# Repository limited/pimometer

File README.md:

pimometer
=========
=======
## Remote Thermocouple Monitor

### Goal 
PCB to report temperature from 4 k-type thermocouples over wireless, for viewing on a smartphone. 
* _Form Factor_: Raspberry Pi Shield
* _Power Source_: Initially battery powered with on/off switch. 
** Future: solar or thermoelectric generator(TEG) using heat from oven.
* _Thermocouple Measurement_: MAX31855 [Datasheet](http://datasheets.maximintegrated.com/en/ds/MAX31855.pdf) via SPI in an SO-8 package
* _Wireless Connection_: WiFi Dongle
* _Configuration/Display_: via SD Card 
** LEDs for display- 1 LED for wireless connection
* Smartphone Display: Ideally would be accessible across multiple smartphone platforms, so no native app. 
** Better to have a webserver run on the device itself, i.e. Flask

### Design
#### Raspberry Pi pinout
* Clock: 11 
* MISO: 9
* CS1: 18 
* CS2: 23
* CS3: 24
* CS4: 25
* Also need +3.3V and ground available to shield
 
#### Software Design
* When Flask receives request for current temperatures, 
o

#### Service installation
chmod 755 nodejs
sudo cp nodejs /etc/init.d
sudo update-rc.d nodejs defaults

### Avahi Installation
sudo apt-get install avahi-daemon
sudo insserv avahi-daemon

#### Cost Comparison
Component  |  Raspberry Pi  | Arduino (TC shield + wifi breakout)
-----------+----------------+-------------------------------------
Controller |   $35          |    $7
Crystal    |                |    $1
Regulator  |                |    $2
Wifi       |   $15          |    $35
SD card    |   $8           |    
------------------------------------------------------------------
Subtotal   |   $58          |    $45

TC shield
------------
4xTC       |              $32
Custom PCB |              $15?

Enclosure    |
LiPo Battery | 
LiPo Charger |

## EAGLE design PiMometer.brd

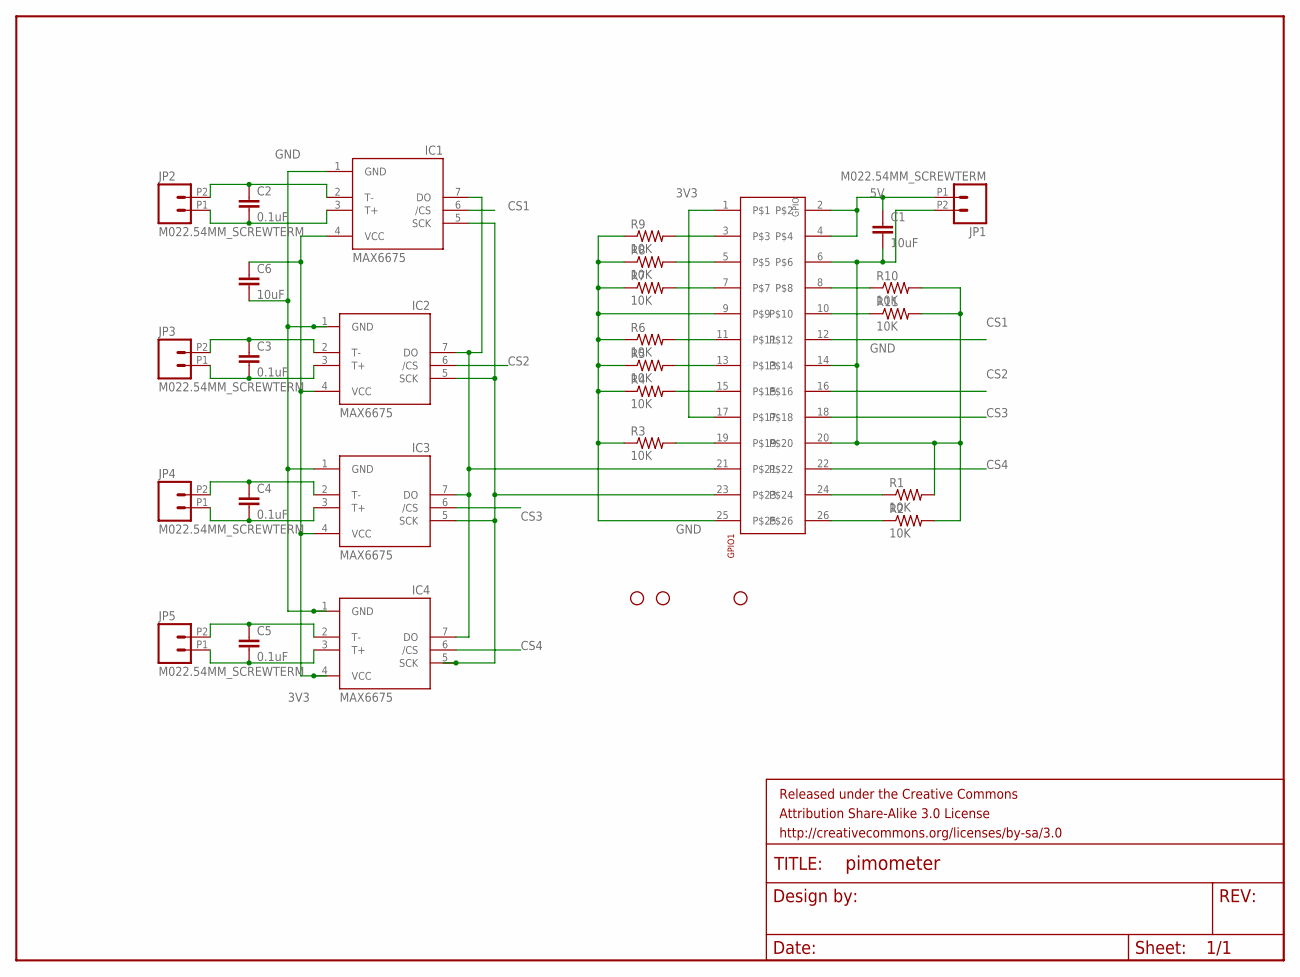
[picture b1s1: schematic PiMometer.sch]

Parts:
C1, C6: 10uF; 1210
C2, C3, C4, C5: 0.1uF; 0603-CAP
FRAME1: FRAME-LETTER; CREATIVE_COMMONS
GPIO1: 2X132X13; 2X13
IC1, IC2, IC3, IC4: MAX6675; SO08
JP1, JP2, JP3, JP4, JP5: M022.54MM_SCREWTERM; 1X02_2.54_SCREWTERM
R1, R2, R3, R4, R5, R6, R7, R8, R9, R10, R11: 10K; 0603-RES
STANDOFF1, STANDOFF2, STANDOFF4: STAND-OFF

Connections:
3V3: C6.1, GPIO1.1, GPIO1.17, IC1.4 (VCC), IC2.4 (VCC), IC3.4 (VCC), IC4.4 (VCC)
5V: C1.1, GPIO1.2, GPIO1.4, JP1.P1 (1)
CS1: GPIO1.12, IC1.6 (/CS)
CS2: GPIO1.16, IC2.6 (/CS)
CS3: GPIO1.18, IC3.6 (/CS)
CS4: GPIO1.22, IC4.6 (/CS)
GND: C1.2, C6.2, GPIO1.6, GPIO1.9, GPIO1.14, GPIO1.20, GPIO1.25, IC1.1 (GND), IC2.1 (GND), IC3.1 (GND), IC4.1 (GND), JP1.P2 (2), R1.2, R2.2, R3.1, R4.1, R5.1, R6.1, R7.1, R8.1, R9.1, R10.2, R11.2
unnamed: GPIO1.21, IC1.7 (DO), IC2.7 (DO), IC3.7 (DO), IC4.7 (DO)
unnamed: GPIO1.23, IC1.5 (SCK), IC2.5 (SCK), IC3.5 (SCK), IC4.5 (SCK)
unnamed: GPIO1.24, R1.1
unnamed: GPIO1.26, R2.1
unnamed: C2.1, IC1.2 (T-), JP2.P2 (2)
unnamed: C2.2, IC1.3 (T+), JP2.P1 (1)
unnamed: GPIO1.3, R9.2
unnamed: GPIO1.5, R8.2
unnamed: GPIO1.7, R7.2
unnamed: GPIO1.11, R6.2
unnamed: GPIO1.13, R5.2
unnamed: GPIO1.15, R4.2
unnamed: GPIO1.19, R3.2
unnamed: GPIO1.8, R10.1
unnamed: GPIO1.10, R11.1
unnamed: C3.1, IC2.2 (T-), JP3.P2 (2)
unnamed: C3.2, IC2.3 (T+), JP3.P1 (1)
unnamed: C4.1, IC3.2 (T-), JP4.P2 (2)
unnamed: C4.2, IC3.3 (T+), JP4.P1 (1)
unnamed: C5.1, IC4.2 (T-), JP5.P2 (2)
unnamed: C5.2, IC4.3 (T+), JP5.P1 (1)

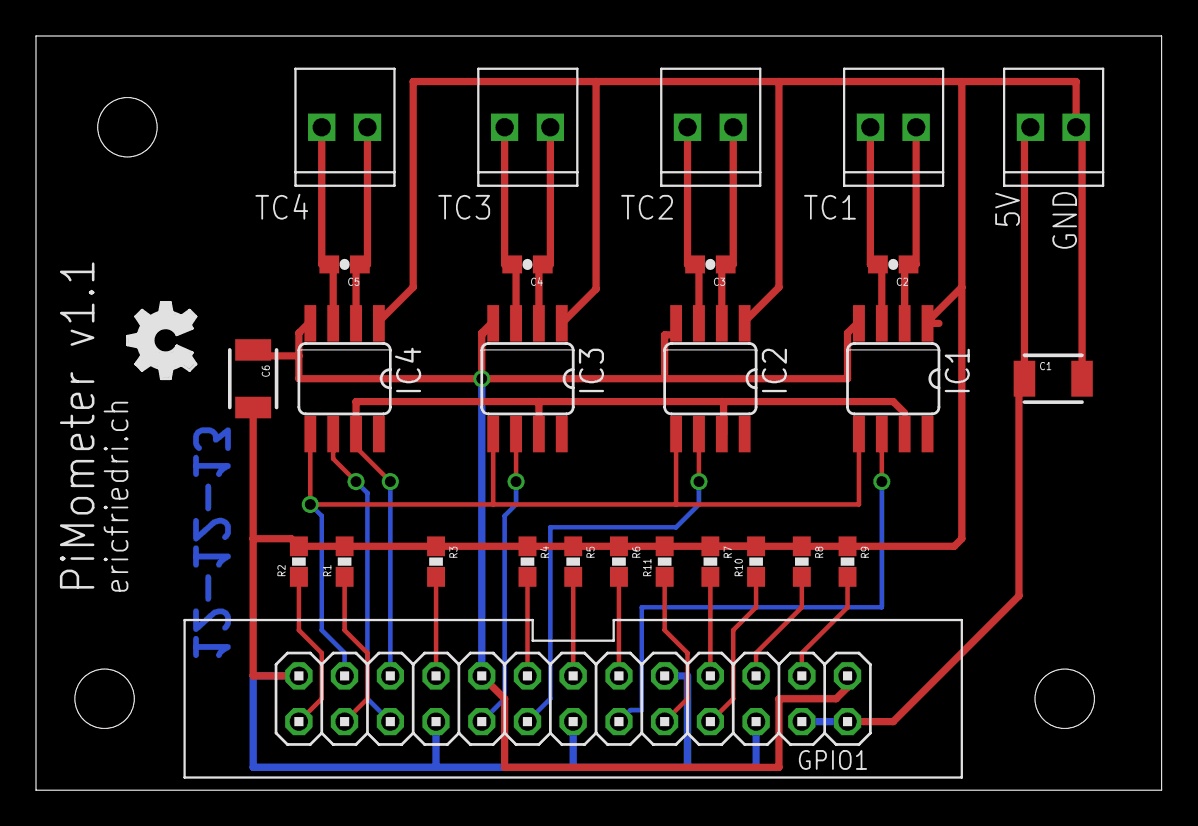
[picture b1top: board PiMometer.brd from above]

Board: 2 copper layers, 62.5 x 41.9 mm, 32 parts (0 on the bottom side), 28 nets.

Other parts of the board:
U$1: OSHW_FILLX150_NOTEXT

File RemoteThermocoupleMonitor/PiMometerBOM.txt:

Partlist exported from /Users/efriedri/Dropbox/eagle/PiMometer/PiMometer.sch at 11/29/13 10:36 PM

(M) Mouser
(SF) Sparkfun

Supplier	Part      Value               Device                  Package             Description                          PROD_ID   VALUE
M		C1        10uF                10UF50V20%(1210)        1210                16V 1210 10uF 10% MLCC	       810-C3225X7R1C106K 10uF 
M		C2        0.1uF               0.1UF-100V-10%(0603)    0603-CAP            16V 0603 .1uF 5% MLCC                77-VJ0603Y104JXJPBC 0.1uF
M		C3        0.1uF               0.1UF-100V-10%(0603)    0603-CAP            16V 0603 .1uF 5% MLCC                77-VJ0603Y104JXJPBC 0.1uFM
M		C4        0.1uF               0.1UF-100V-10%(0603)    0603-CAP            16V 0603 .1uF 5% MLCC                77-VJ0603Y104JXJPBC 0.1uF
M		C5        0.1uF               0.1UF-100V-10%(0603)    0603-CAP            16V 0603 .1uF 5% MLCC                77-VJ0603Y104JXJPBC 0.1uF
M		C6        10uF                10UF50V20%(1210)        1210                16V 1210 10uF 10% MLCC               810-C3225X7R1C106K 10uF                                    
SF		GPIO1     2X132X13            2X132X13                2X13                PRT-11490                            PRT-11490                                                      
M		IC1       MAX31855            MAX31855 		      SO08      	  MAX31855KASA+                                                              
M		IC2       MAX31855            MAX31855                SO08                MAX31855KASA+                                                    
M		IC3       MAX31855            MAX31855                SO08                MAX31855KASA+                                       
M		IC4       MAX31855            MAX31855                SO08                MAX31855KASA+                                       
SF		JP1       M022.54MM_SCREWTERM M022.54MM_SCREWTERM     1X02_2.54_SCREWTERM PRT-10571				PRT-10571	                
SF		JP2       M022.54MM_SCREWTERM M022.54MM_SCREWTERM     1X02_2.54_SCREWTERM PRT-10571				PRT-10571
SF		JP3       M022.54MM_SCREWTERM M022.54MM_SCREWTERM     1X02_2.54_SCREWTERM PRT-10571				PRT-10571
SF		JP4       M022.54MM_SCREWTERM M022.54MM_SCREWTERM     1X02_2.54_SCREWTERM PRT-10571				PRT-10571
SF 		JP5       M022.54MM_SCREWTERM M022.54MM_SCREWTERM     1X02_2.54_SCREWTERM PRT-10571				PRT-10571
SF		R1        10K                 10KOHM1/10W1%(0603)0603 0603-RES            RES-00824                            PRT-11246 10K        
SF 		R2        10K                 10KOHM1/10W1%(0603)0603 0603-RES            RES-00824                            PRT-11246 10K
SF 		R3        10K                 10KOHM1/10W1%(0603)0603 0603-RES            RES-00824                            PRT-11246 10K  
SF 		R4        10K                 10KOHM1/10W1%(0603)0603 0603-RES            RES-00824                            PRT-11246 10K  
SF 		R5        10K                 10KOHM1/10W1%(0603)0603 0603-RES            RES-00824                            PRT-11246 10K  
SF 		R6        10K                 10KOHM1/10W1%(0603)0603 0603-RES            RES-00824                            PRT-11246 10K  
SF 		R7        10K                 10KOHM1/10W1%(0603)0603 0603-RES            RES-00824                            PRT-11246 10K  
SF 		R8        10K                 10KOHM1/10W1%(0603)0603 0603-RES            RES-00824                            PRT-11246 10K  
SF 		R9        10K                 10KOHM1/10W1%(0603)0603 0603-RES            RES-00824                            PRT-11246 10K  
SF 		R10       10K                 10KOHM1/10W1%(0603)0603 0603-RES            RES-00824                            PRT-11246 10K  
SF 		R11       10K                 10KOHM1/10W1%(0603)0603 0603-RES            RES-00824                            PRT-11246 10K  
N/A		STANDOFF1 STAND-OFF           STAND-OFF               STAND-OFF           #4 Stand Off                                        
N/A		STANDOFF2 STAND-OFF           STAND-OFF               STAND-OFF           #4 Stand Off                                        
N/A		STANDOFF4 STAND-OFF           STAND-OFF               STAND-OFF           #4 Stand Off

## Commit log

2013-10-16 Added some CheckLiverLight case design files Started project descriptor of Remote Thermocouple Monitor
2013-10-24 More updates to README.md
2013-12-01 Added a bunch of new projects, consolidating from Dropbox and local directories. Some personal scripts/projects from Cisco Remote Thermocouple Monitor (i.e. PiMometer) Reverse Geocache Temp Controlle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
2013-12-12 First pass of UI code for Pimometer, built on Node.js, socket.io, and d3s
2014-01-28 Added package.json and rpi.js
2014-01-28 Filter branch
2014-01-28 Removing RemoteThermocoupleMonitor directory
2014-01-29 Fixed some of the (surely many) bugs in rpi.js. Event driven does not seem to be a good way to access GPIO ports
2014-01-29 Got code working with 1 channel and MAX31855 breakout board. Issue with scope of channel variable in tempstate timer callback
2014-01-31 Complete Pimometer Next step: error displays?
2014-01-31 Fix incorrect variable name in tempstate.js Convert temp to F in ThermocoupleRead.py Start node as root for access to port 80
2016-07-18 Add conversion function to allow use with MAX31855K and a TypeJ Thermocouple

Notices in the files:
parts and their libraries:
SparkFun-Resistors: Licensing: CC v3.0 Share-Alike You are welcome to use this library for commercial purposes.
SparkFun-Aesthetics: Released under the Creative Commons Attribution Share-Alike 3.0 License
SparkFun-Aesthetics: http://creativecommons.org/licenses/by-sa/3.0
